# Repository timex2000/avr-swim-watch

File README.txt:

7.0

Split the main.c file into separate files to make future editing a bit easier.

-------------------------------------------------

6.0

04-10-2014

Added the ability to record and view multiple sessions.

The history can be deleted, but currently only in one block, rather than choosing to delete different sessions.

Each session takes up 255 bytes of memory in the EEPROM, with the possibility of (255-9) lengths possible. The other nine are used to store the date, time, total time, and number of lengths. Since I'm using 64K bit EEPROM, this gives a possible memory of 31 sessions.

The menus are still a bit messy, but will look at improving them soon

-------------------------------------------------

5.0

Using function pointers in the FSM model.

Added ability to update time manually which is then uploaded to the FSM.

-------------------------------------------------

3.0

First stage of battery charging and management.

Using the "programmable" MCP73832 to control the current flow to the battery during charging. The signal from this is connected to the uC so I know then the battery if fully charged.

Also using the DS2782 fuel gauge IC. The IC can be communicated to via i2c. I use this to read the current accumulation as a measure of the current capacity of the battery during use and charging.

When the device is being charged, there's a detected "charging display" which will show the current amount. When the battery is fully charged, the current accomulated value is stored as the current max capacity of the battery as this will reduce over time.

----------------------------------------------------------------------------

SportsWatch 2.0

First design of the swim watch pyscially built.

Physical circuit built on perf-board (it and the circuit diagram included).

User interface has been uploaded to be more useful in the pool.

Code has been cleaned up and the interrupt handlers now do as little as possible and all display updates have been moved to the main loop.

----------------------------------------------------------------------------

SportsWatch 1.0
	
Software developed and tested on avr-gcc using avrdude (testing on both Windows 8.1 and Raspberry Pi).

This is still in early development stage, so many bugs and issues with the code.

The program uses u8glib and 24l64 libraries to control the OLED display and EEPROM respectively.

First full draft of the swim watch on breadboard. Features include:
	
	- Currently all hardware is on a breadboard, and powered (and programmed) using a Raspberry Pi. 
	- Using 0.96" OLED display
	- There are 3 buttons which are used for navigation and running
	- An external 16MHz crystal is used with no divide by 8
	- A 24LC64 EEPROM is used to store one swim
	- The OLED display and the EEPROM memory are both I2C controlled
	
	- Using u8glib to control the OLED display
	- On startup, the device goes straight to main menu containing two options:
		- Show the previous swim session
		- Record a new session
	- A simple switch based Finite State Machine is used to navigate the system (including the menu, showing the previous swim, and recording the current one)
	- When showing the previous swim, each length can be shown - one at a time - by pressing the up or down buttons (return to the main menu using the select button)
	- The display shows the selected length's time in hh:mm:ss (need to remove the hh)
	- When going from main menu to record new swim, a new swim session is started and recorded to the EEPROM.
	- New lengths are recorded by pressing the select button (return to the main menu using the up or down buttons)
	- The previous length time and total time of the current swim are shown in hh:mm:ss format
	- Number of lengths, and length times are stored as uint8, whereas the total swim time is stored in uint16
	- Timer1 interrupt is set for every 0.1 sec, potentially giving 0.1 accuracy, though at the moment, the length times are stored with 1 sec resolution

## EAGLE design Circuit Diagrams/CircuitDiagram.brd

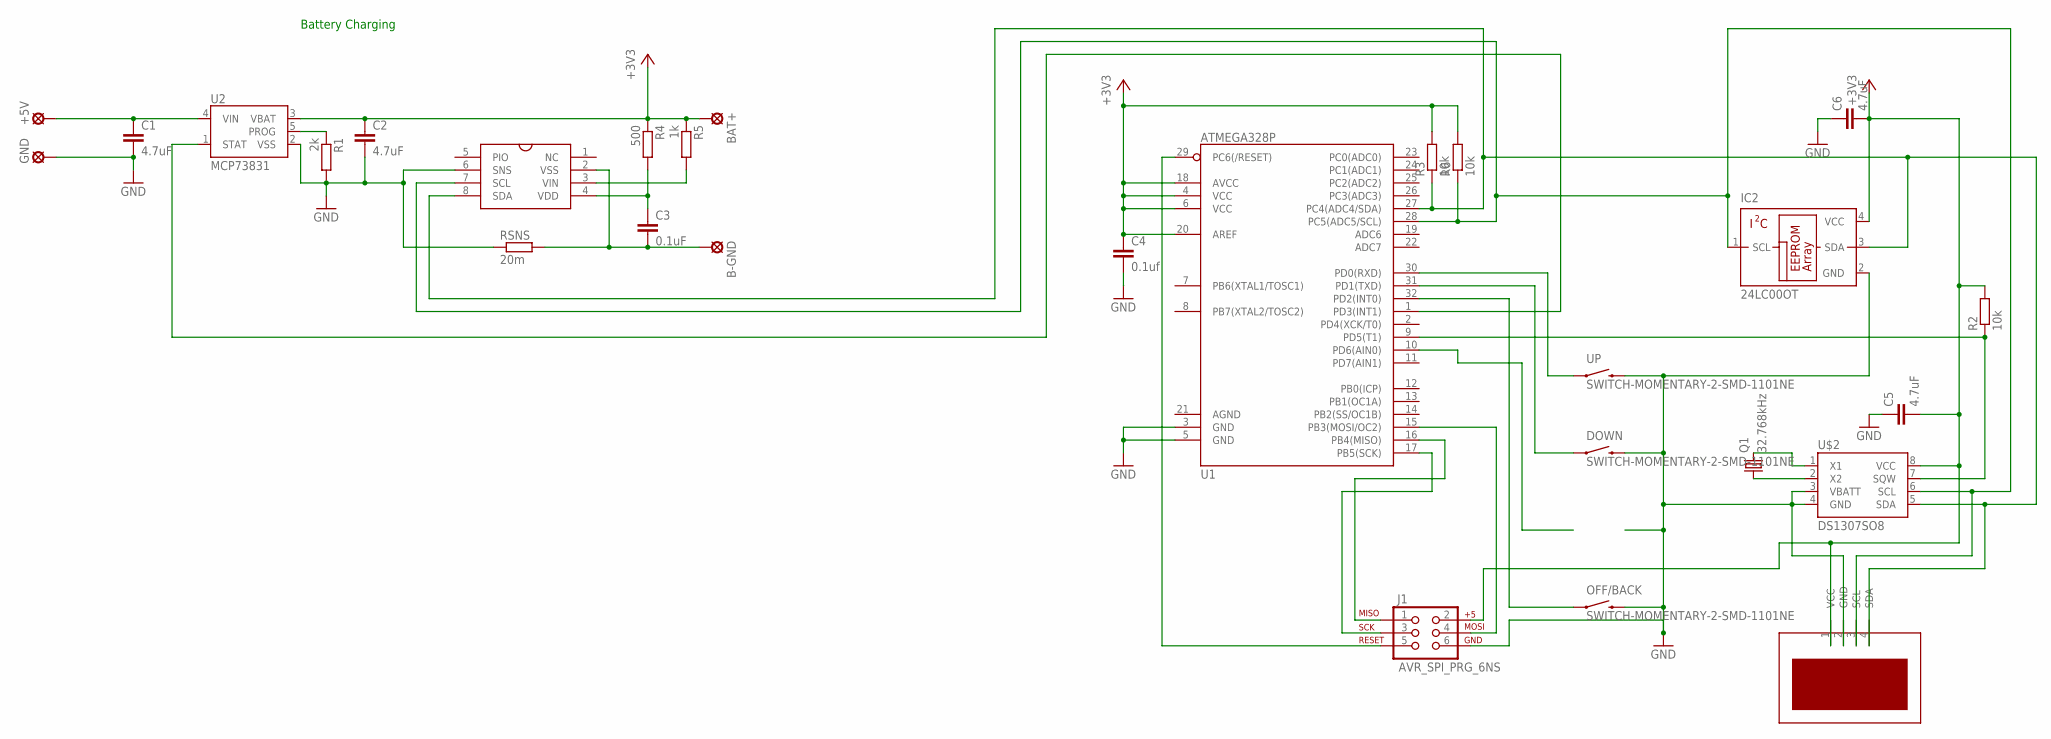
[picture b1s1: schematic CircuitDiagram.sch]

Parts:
+5V: LSP10
B-GND: LSP10
BAT+: LSP10
C1, C2, C5: 4.7uF; C0402
C3: 0.1uF; C0402
C4: 0.1uf; C0402
C6: 4.7uF; C1005
DOWN: SWITCH-MOMENTARY-2-SMD-1101NE; TACTILE-SWITCH-1101NE
GND: LSP10
IC2: 24LC00OT; SOT23-5L
J1: AVR_SPI_PRG_6NS; 2X3-NS
OFF/BACK: SWITCH-MOMENTARY-2-SMD-1101NE; TACTILE-SWITCH-1101NE
Q1: 32.768kHz; 3.2X1.5-2-PAD
R1: 2k; R0603
R2, R3, R6: 10k; R0603
R4: 500; R0603
R5: 1k; R0603
RSNS: 20m; R0603
U1: ATMEGA328P; TQFP32-08
U2: MCP73831; SOT23-5
U$1: DS2782-2; TSSOP8
U$2: DS1307SO8; SO08
U$3: OLED
UP: SWITCH-MOMENTARY-2-SMD-1101NE; TACTILE-SWITCH-1101NE

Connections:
5V: +5V.MP, C1.1, U2.4 (VIN)
+3V3: BAT+.MP, C2.1, C4.1, C5.2, C6.2, IC2.4 (VCC), J1.2, R2.2, R3.2, R4.1, R5.1, R6.2, U1.4 (VCC), U1.6 (VCC), U1.18 (AVCC), U1.20 (AREF), U2.3 (VBAT), U$2.8 (VCC), U$3.1 (VCC)
GND: C1.2, C2.2, C4.2, C5.1, C6.1, DOWN.2, GND.MP, IC2.2 (GND), J1.6, OFF/BACK.2, R1.2, RSNS.1, U1.3 (GND), U1.5 (GND), U2.2 (VSS), U$1.6 (SNS), U$2.3 (VBATT), U$2.4 (GND), U$3.2 (GND), UP.2
unnamed: R1.1, U2.5 (PROG)
unnamed: IC2.1 (SCL), R6.1, U1.28 (PC5(ADC5/SCL)), U$1.7 (SCL), U$2.6 (SCL), U$3.3 (SCL)
unnamed: R5.2, U$1.3 (VIN)
unnamed: C3.1, R4.2, U$1.4 (VDD)
unnamed: B-GND.MP, C3.2, RSNS.2, U$1.2 (VSS)
unnamed: IC2.3 (SDA), R3.1, U1.27 (PC4(ADC4/SDA)), U$1.8 (SDA), U$2.5 (SDA), U$3.4 (SDA)
unnamed: U1.1 (PD3(INT1)), U2.1 (STAT)
unnamed: U1.30 (PD0(RXD)), UP.1
unnamed: DOWN.1, U1.31 (PD1(TXD))
unnamed: OFF/BACK.1, U1.32 (PD2(INT0))
unnamed: Q1.2, U$2.1 (X1)
unnamed: Q1.1, U$2.2 (X2)
unnamed: R2.1, U1.9 (PD5(T1)), U$2.7 (SQW)
unnamed: J1.1, U1.16 (PB4(MISO))
unnamed: J1.3, U1.17 (PB5(SCK))
unnamed: J1.4, U1.15 (PB3(MOSI/OC2))
unnamed: J1.5, U1.29 (PC6(/RESET))

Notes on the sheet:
Battery Charging

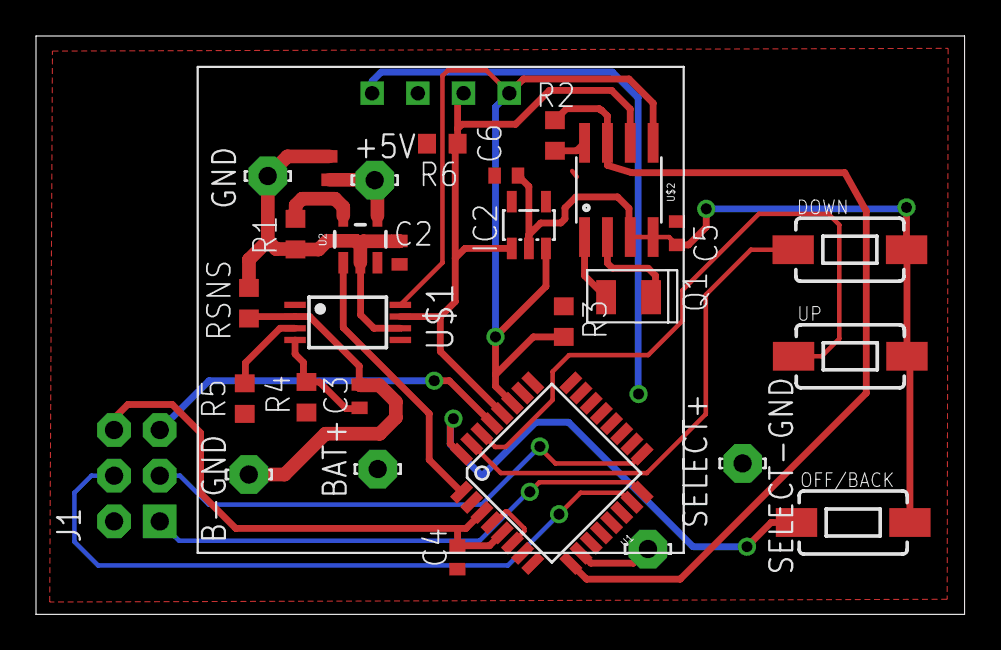
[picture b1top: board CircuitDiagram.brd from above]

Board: 2 copper layers, 51.6 x 32.1 mm, 30 parts (0 on the bottom side), 20 nets.

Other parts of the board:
SELECT+: LSP10
SELECT-GND: LSP10

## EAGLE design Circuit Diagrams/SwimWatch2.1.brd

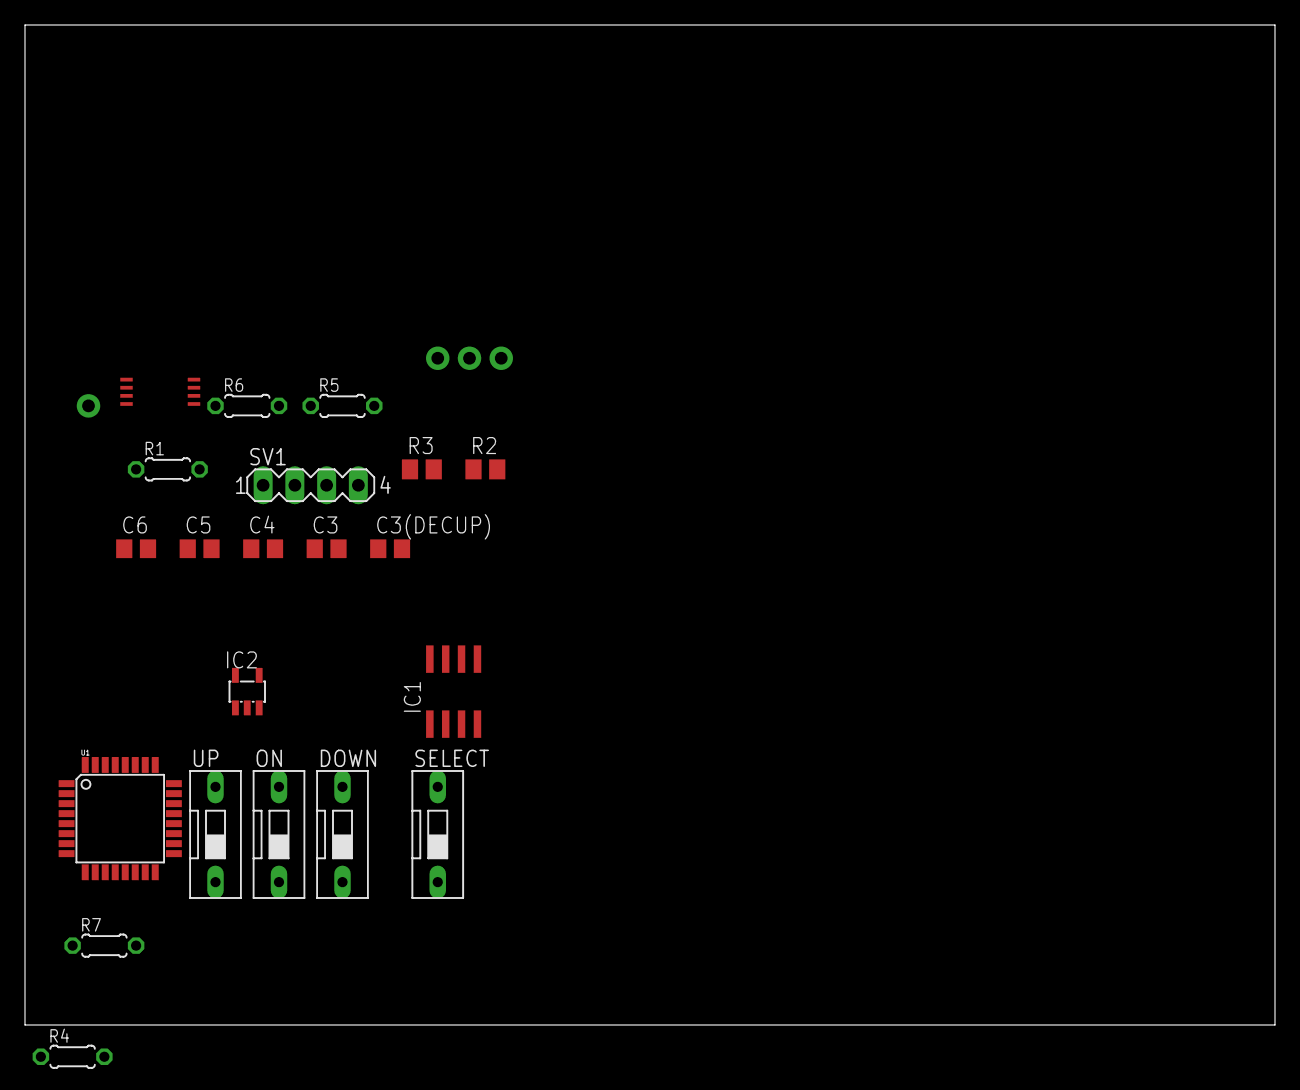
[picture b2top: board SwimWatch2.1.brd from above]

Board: 2 copper layers, 100.0 x 80.0 mm, 25 parts (0 on the bottom side), 15 nets, no tracks yet.

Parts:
BAT+VE: M01NOSILK-KIT; 1X01NS-KIT
BAT_GND: M01NOSILK-KIT; 1X01NS-KIT
C3, C4, C5, C6: 1uF; C0805
C3(DECUP): 0.1uF; C0805
CHARGE+VE: M01NOSILK-KIT; 1X01NS-KIT
DOWN: DS-01
GND: M01NOSILK-KIT; 1X01NS-KIT
IC1: 24LC64SN; SO-08
IC2: MCP73831/OT; SOT23-5L
ON: DS-01
R1: 20mOhm; 0204/5
R2, R3: 1K; M0805
R4: 0204/5
R5: 500; 0204/5
R6: 1k; 0204/5
R7: 5k; 0204/5
SELECT: DS-01
SV1: MA04-1
U1: ATMEGA328P; TQFP32-08
U$1: DS2782
UP: DS-01

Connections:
+3V3: BAT+VE.1, C3(DECUP).2, C4.2, C5.1, C6.2, IC1.8, IC2.3, R2.2, R3.2, R4.2, R5.2, R6.2, SV1.1, U1.4, U1.6
DOWN: DOWN.1, U1.31
GND: C3(DECUP).1, C5.2, C6.1, DOWN.2, IC1.1, IC1.2, IC1.3, IC1.4, ON.2, R1.1, SELECT.2, SV1.2, U1.3, U1.5, U$1.7, UP.2
unnamed: IC2.1, R4.1, U1.1
unnamed: U1.30, UP.1
unnamed: IC2.5, R7.2
unnamed: ON.1, U1.32
unnamed: SELECT.1, U1.2
unnamed: C3.2, CHARGE+VE.1, IC2.4
unnamed: C4.1, IC2.2, R7.1
unnamed: BAT_GND.1, R1.2, R5.1, U$1.2, U$1.4
unnamed: R6.1, U$1.3
unnamed: C3.1, GND.1
SCL: IC1.6, SV1.3, U1.28, U$1.6
SDA: IC1.5, R2.1, R3.1, SV1.4, U1.27, U$1.5

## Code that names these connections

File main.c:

/*
	SwimWatch 7.0
*/

#include <avr/io.h>
#include <util/delay.h>
#include <avr/interrupt.h>
#include <stdio.h>
	
#include "u8g.h"
#include "24c64.h"
#include "twi.h"
#include "fsm.h"
#include "menu.h"
#include "fsmFunctions.h"
				
#define NUMBUTTONS 6
#define CHARGE PD2
#define OFF PD3
#define UP PD0
#define DOWN PD1
#define CLK PD5
#define SELECT PD4

extern stateElement stateMatrix[29][8];

volatile uint8_t pressed[NUMBUTTONS], justPressed[NUMBUTTONS], justReleased[NUMBUTTONS], timePressed[NUMBUTTONS];

event getEvent(void){
	event e = Nothing;
	uint8_t longPress = 20;
	
	if (justReleased[2]){
		justReleased[2] = 0;
		e = UpPressed;
	}
	else if (justReleased[3]){
		justReleased[3] = 0;
			e = DownPressed;
	}
	else if (justPressed[5] & (timePressed[5] < longPress) & justReleased[5]){
		justPressed[5] = 0;
		timePressed[5] = 0;
		justReleased[5] = 0;
		e = SelectPressed;
	}
	else if (justReleased[5]){
		justReleased[5] = 0;
	}
	else if (justReleased[0] & (timePressed[0] < longPress)){
		justReleased[0] = 0;
		e = BackPressed;
	}
	else if (pressed[0] & (timePressed[0] > longPress)){
		//justReleased[0] = 0;
		timePressed[0] = 0;
		e = OffPressed;
	}
	else if (pressed[5] & (timePressed[5] > longPress)){
		e = SelectLongPressed;
		timePressed[5] = 0;
		justReleased[5] = 0;
		justPressed[5] = 0;
		//pressed[5] = 0;
	}
	else if (justReleased[4]){
		justReleased[4] = 0;
		e = ClkPressed;
	}
	
	
	
	/*if (pressed[0] & timePressed[0] > 10){
		//justReleased[0] = 0;
		e = OFF_PRESSED;
	}
	else if (justReleased[0] & timePressed[0] < 10){
		justReleased[0] = 0;
		e = BACK_PRESSED;
	}
	else if (justPressed[1]){
		justPressed[1] = 0;
		e = CHARGER_IN;
	}
	else if (justReleased[1]){
		justReleased[1] = 0;
		e = CHARGER_OUT;
	}
	else if (justReleased[2]){
		justReleased[2] = 0;
		e = UP_PRESSED;
	}
	else if (justReleased[3]){
		justReleased[3] = 0;
		e = DOWN_PRESSED;
	}
	else if (justReleased[4]){
		justReleased[4] = 0;
		e = CLK_PRESSED;
	}
	else if (justReleased[5]){
		justReleased[5] = 0;
		e = SELECT_PRESSED;
	}
	*/
	return e;
}


// Initialise timer1 which is used for checking the buttons
void initTimer1(void){
	TCCR1A = (1 << WGM12);
	TCCR1B = (1 << CS11) | (1 << CS10) | (1 << WGM12);				// 64 prescaler
	TIMSK1 = (1 << OCIE1A);
	/* 8MHZ / 64 = 125,000Hz = 0.000008 sec
		(15ms) / (0.000008) = 1875
		(# timer counts) = 1875 - 1 = 1874 */
	OCR1A = 1874;
}

// Initialise the ports
void initPorts(void){
	DDRD = 0x00;
	PORTD = 0xFF;
}

// Sets the number of sessions to zero when the battery is pulled out (might remove this later)
void initMemory(void){
	EEOpen();
	EEWriteByte(2, 0);	// Zero sessions recorded.
}

// Initialise the system
void initSystem(void){
	initPorts();
	initOLED();	
	initTimer1();
	sei();
}

// Converts time into string to be printed in format hh:mm:ss
void timeToString(uint16_t time, char *rS){
	// Calculating the required values
	uint8_t seconds = time % 60;
	time /= 60;
	uint8_t minutes = time % 60;
	time /= 60;
	uint8_t hourss = time;
	
	// Converting the values into different strings
	char strHours[3], strMins[3], strSecs[3];
	//convertTime(lastLengthTime);
	itoa(hourss, strHours, 10);
	itoa(minutes, strMins, 10);
	itoa(seconds, strSecs, 10);
	
	// Combining the strings together into one.
	// Sure there must be a better way to do this!
	if (hourss < 1){
		rS[0] = '0';
		rS[1] = '0';
	}
	else if (hourss < 10){
		rS[0] = '0';
		rS[1] = strHours[0];
	}
	else{
		rS[0] = strHours[0];
		rS[1] = strHours[1];
	}
	rS[2] = ':';
	if (minutes < 1){
		rS[3] = rS[4] = '0';
	}
	else if (minutes < 10){
		rS[3] = '0';
		rS[4] = strMins[0];
	}
	else{
		rS[3] = strMins[0];
		rS[4] = strMins[1];
	}
	rS[5] = ':';
	if (seconds < 10){
		rS[6] = '0';
		rS[7] = strSecs[0];
	}
	else{
		rS[6] = strSecs[0];
		rS[7] = strSecs[1];
	}
	rS[8] = 0x00;
}

uint8_t divu10(uint8_t n){
		uint16_t q, r;
		
		q = (n >> 1) + (n >> 2);
		q = q + (q >> 4);
		q = q + (q >> 8);
		q = q + (q >> 16);
		q = q >> 3;
		r = n - q*10;
		return q + ((r + 6) >> 4);
}

// Convert uint8_t to char*
// Max value of uint8_t is 255
char* my_uitoa_10(uint8_t value, char *string){
	if (!string)
		return NULL;

	uint8_t c = 0;
	uint8_t size = 0;
	
	if (value >= 100)
		size = 2;
	else if (value >= 10)
		size = 1;
	else
		size = 0;
	string[size+1] = '\0';
	for (uint8_t i = size; i > 0; i--){
		c = value % 10;
		string[i] = '0' + c;
		value /= 10;
		//value = divu10(value);
	}
	string[0] = '0' + value;
			
	return string;	
}

// Checking the inputs for button presses and performing the debouncing
void checkSwitches(void){
	static uint8_t previousState[NUMBUTTONS];
	static uint8_t currentState[NUMBUTTONS];
	static uint16_t lastTime;
	uint8_t index;
	uint8_t input = PIND;
	uint8_t inputCheck[] = {OFF, CHARGE, UP, DOWN, CLK, SELECT};
	
	if (lastTime++ < 4){ // 15ms * 4 debouncing time
		return;
	}
	
	lastTime = 0;
	for (index = 0; index < NUMBUTTONS; index++){		
		if (!(input & (1 << inputCheck[index])))
			currentState[index] = 0;
		else
			currentState[index] = 1;
		
		if (currentState[index] == previousState[index]) {
			if ((pressed[index] == 0) && (currentState[index] == 0)) {
			// just pressed
			justPressed[index] = 1;
			timePressed[index] = 0;
			}
			else if ((pressed[index] == 1) && (currentState[index] == 1)) {
				// just released
				justReleased[index] = 1;
			}
			pressed[index] = !currentState[index];  // remember, digital HIGH means NOT pressed
			if (pressed[index])
				timePressed[index]++;
		}
		previousState[index] = currentState[index];   // keep a running tally of the buttons
	}	
}

// Used to check for button presses and releases
ISR (TIMER1_COMPA_vect){
	checkSwitches();
}

// Used to wake up the device
ISR(INT1_vect){
}

// Used for the charging interrupt
ISR(INT0_vect){
}

int main(void){
	state currentState = StateStart;
	action actionToDo = NoAction;
	
	// Function pointer test
	void (*actionables[64])(void) = {noAction, startSystem, showMenuHistory, showMenuRecord, showMenuSystem, showTimeChangeMenu, showMenuSystemShow, switchOffSystem, showSystemVersion, startD0Change, increaseD0, decreaseD0, startD1Change, increaseD1, decreaseD1, startMo0Change, increaseMo0, decreaseMo0, startMo1Change, increaseMo1, decreaseMo1, startY0Change, increaseY0, decreaseY0, startY1Change, increaseY1, decreaseY1, startH0Change, increaseH0, decreaseH0, startH1Change, increaseH1, decreaseH1, startMi0Change, increaseMi0, decreaseMi0, startMi1Change, increaseMi1, decreaseMi1, startS0Change, increaseS0, decreaseS0, startS1Change, increaseS1, decreaseS1, storeDateTime, showRecordWait, startRecordingSwim, showHistoryOverview, addLength, addLastLength, updateRecordTime, showFirstLength, showNextLength, showPreviousLength, showNextSession, showPreviousSession, showLastHistory, showHistoryMenuShow, showHistoryMenuDelete, showHistoryMenuDetails, showHistoryDeleteConfirm, deleteHistory, showHistoryDetails};
	
	while(1){
		event e = getEvent();
		
		// Obtain the next action
		stateElement stateEvaluation = stateMatrix[currentState][e];
		currentState = stateEvaluation.nextState;
		actionToDo = stateEvaluation.actionToDo;
		
		(*actionables[actionToDo])();		
	}
}

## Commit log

2014-07-02 Initial directory structure.
2014-07-02 Upload test
2014-07-02 Second attempt
2014-07-02 SwimWatch1.0 first upload
2014-09-10 Upload of SwimWatch 3.3
2015-07-05 Migrating wiki contents from Google Code

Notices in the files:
parts and their libraries:
SparkFun-Electromechanical: Licensing: Creative Commons ShareAlike 4.0 International - https://creativecommons.org/licenses/by-sa/4.0
